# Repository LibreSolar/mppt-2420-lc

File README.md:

# MPPT Charger 20A

 Outdated design, development of new revision ongoing.

**Important:** As we are currently developing a new revision of this charge controller with several improvements, it is not recommended to rebuild this device anymore. Please see [this forum thread](https://talk.libre.solar/t/community-development-of-new-20a-mppt/121) and feel free to contribute your ideas.

## Features:
- 20A MPPT charger (buck converter)
- 55V max PV input
- 12V or 24V battery output
- 32bit ARM MCU (STM32F072)
- CAN communication interface with CANopen standard RJ45 jacks (including 10V power supply)
- Expandable via Olimex Universal Extension Connector (UEXT) featuring I2C, Serial and SPI interface (e.g. used for display, WIFI communication, etc.)
- Compatible to Hammond Mfg 1591XXCFL housing
- 5V switchable signal output
- USB connector for programming etc.
- Can be used as boost converter with software change
- Suitable for Li-Ion batteries with BMS (even recharge after low voltage disconnect possible, as the charge controller increases the voltage automatically when enoug sunlight is available)

## Built-in protection:
- Overvoltage
- Undervoltage
- Overcurrent
- PV short circuit
- PV reverse polarity (for max. module open circuit voltage of around 40V)
- Battery reverse polarity (destructive, fuse is blown)

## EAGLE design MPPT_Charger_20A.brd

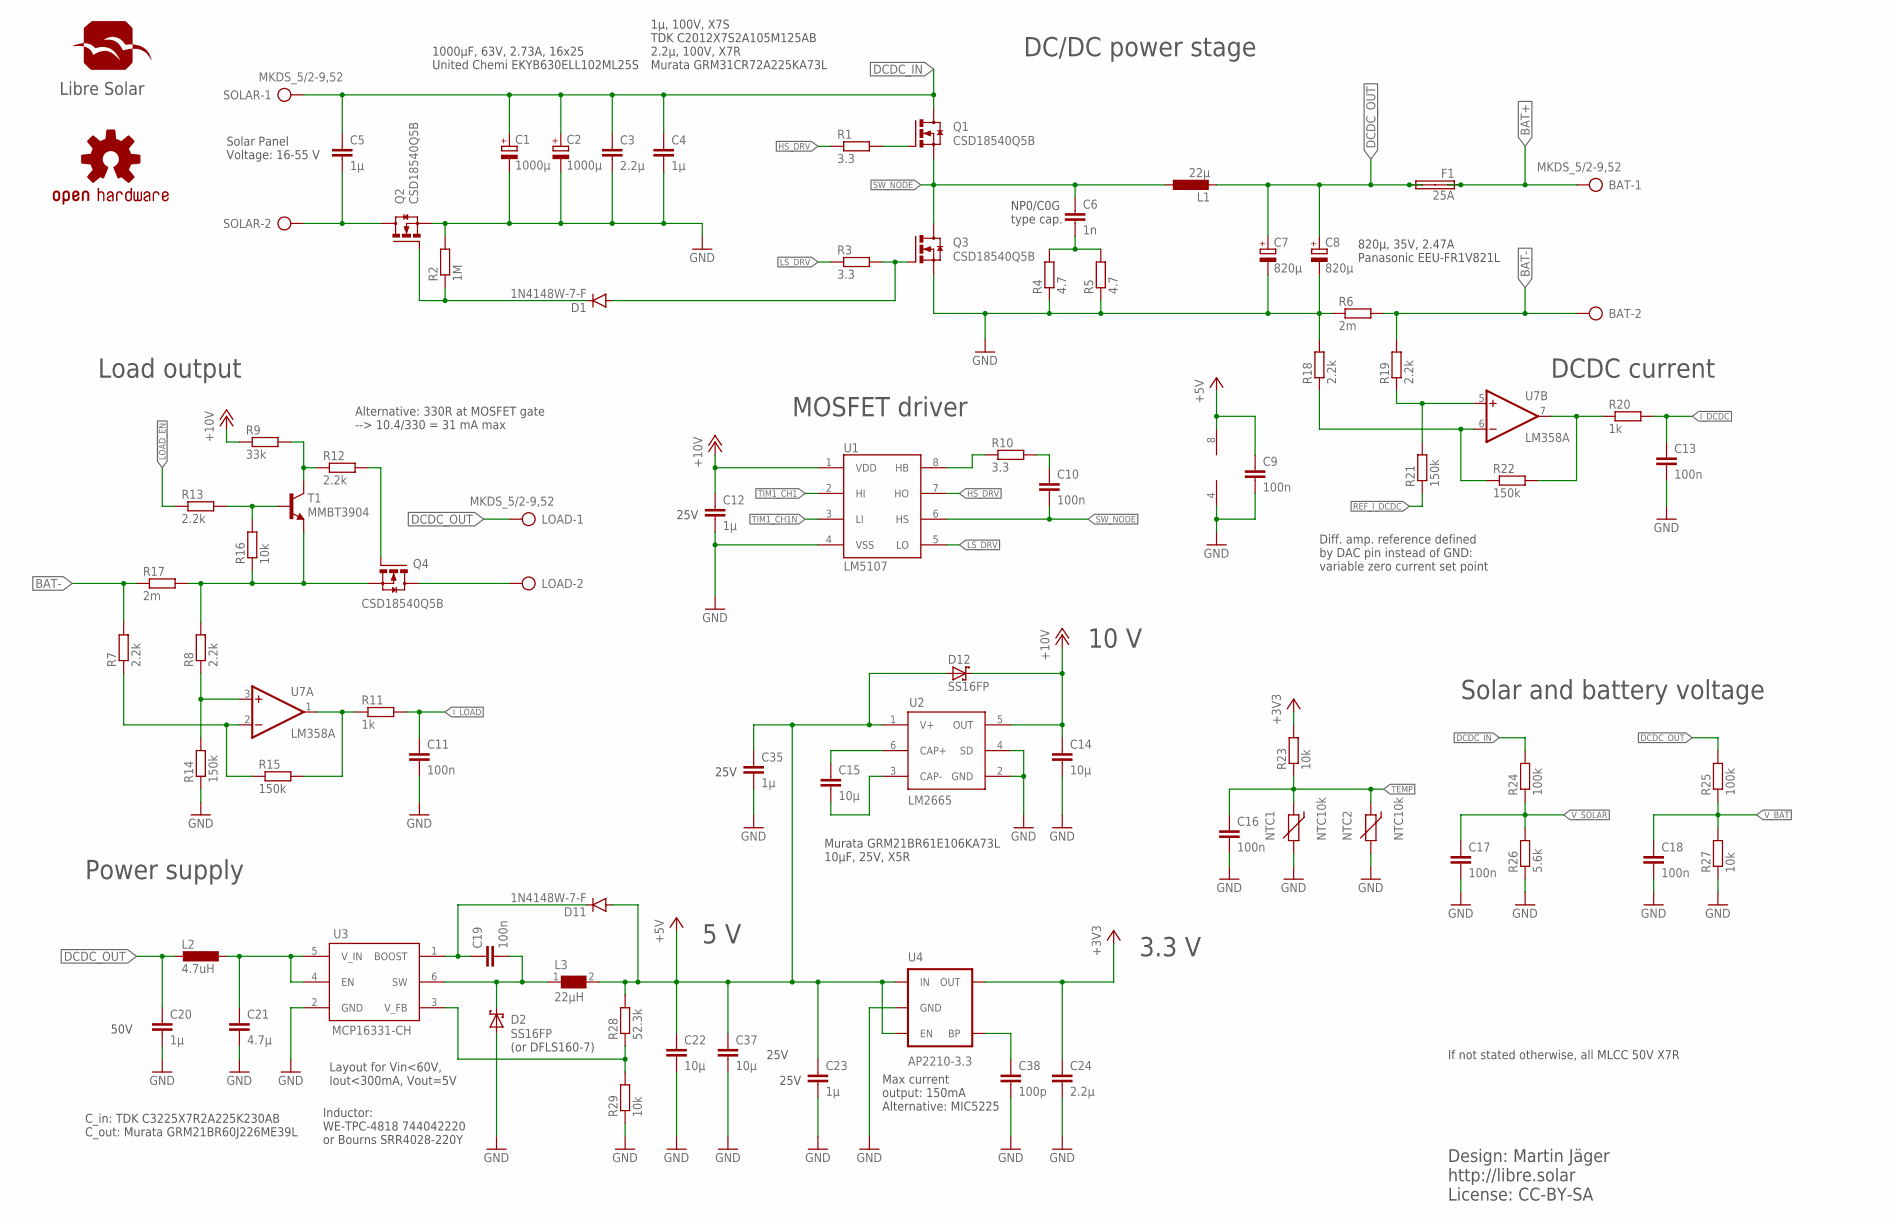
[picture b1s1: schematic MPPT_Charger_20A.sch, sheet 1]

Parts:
BAT: MKDS_5/2-9,52; MKDS_5/2-952; MPN_ALT 691250910002
C1, C2: 1000µ; E7,5-16; MPN EKYB630ELL102ML25S
C3: 2.2µ; C1210
C4, C5, C20: 1µ; C0805
C6: 1n; C0805
C7, C8: 820µ; E5-10,5
C9, C10, C11, C13, C16, C17, C18, C19: 100n; C0603
C12, C23, C35: 1µ; C0603
C14, C15, C22, C37: 10µ; C0805; MPN GRM21BR61E106KA73L
C21: 4.7µ; C1210; MPN GRM31CR71H475KA12L
C24: 2.2µ; C0603; MPN 0805YC475KAT2A
C38: 100p; C0603
D1, D11: 1N4148W-7-F; SOD-123; MPN 1N4148W
D2, D12: SS16FP; POWERDI123; MPN DFLS1100-7
F1: 25A; KEYSTONE-FUSE-3557-2; MPN 3557-2
L1: 22µ; L-FERYSTER-DTMSS-27/0,033/20
L2: 4.7uH; L2012C; MPN 74476404
L3: 22µH; WE-TPC_4818/4828; MPN 744043470
LOAD: MKDS_5/2-9,52; MKDS_5/2-952
N1: OSHW-LOGOM; OSHW-LOGO-M
NTC1, NTC2: NTC10k; R0603@1; MPN NTCG163JF103FT1S
Q1, Q2, Q3, Q4: CSD18540Q5B; 5X6_MOSFET; MPN CSD18540Q5BT
R1, R3, R10: 3.3; R0805; MPN CR0805-FX-1001ELF
R2: 1M; R0603
R4, R5: 4.7; R1206
R6, R17: 2m; R2512; MPN CRE2512-FZ-R002E-3
R7, R8, R12, R13, R18, R19: 2.2k; R0603
R9: 33k; R0603
R11, R20: 1k; R0603
R14, R15, R21, R22: 150k; R0603
R16, R23, R27, R29: 10k; R0603
R24, R25: 100k; R0603
R26: 5.6k; R0603
R28: 52.3k; R0603; MPN CR0805-FX-1001ELF
SOLAR: MKDS_5/2-9,52; MKDS_5/2-952; MPN_ALT 691250910002
T1: MMBT3904; SOT23-BEC; MPN MMBT3904-7-F
U1: LM5107; SOIC-8-N
U2: LM2665; SOT23-6
U3: MCP16331-CH; SOT23-6; MPN MCP16331T-E/CH
U4: AP2210-3.3; SOT23-5; MPN MIC5225-3.3YM5-TR
U7: LM358A; SOIC-8-N
U$1: LIBRESOLAR_LOGO

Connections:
!LOAD_EN!: R13.1; also elsewhere on the board
+3V3: C24.1, R23.2, U4.5 (OUT); also elsewhere on the board
+5V: C9.1, C22.1, C23.1, C35.1, C37.1, D11.A, D12.A, L3.2, R28.2, U2.1 (V+), U4.1 (IN), U4.3 (EN), U7.8 (V+); also elsewhere on the board
+10V: C12.1, C14.1, D12.C, R9.1, U1.1 (VDD), U2.5 (OUT)
BAT+: BAT.1, F1.P$1 (1A), F1.P$2 (1B)
BAT-: BAT.2, R6.2, R7.2, R17.1, R19.2
BAT-1: Q4.S1 (S), Q4.S2 (S), Q4.S3 (S), R8.2, R16.1, R17.2, T1.E
DCDC_IN: C1.+, C2.+, C3.1, C4.1, C5.1, Q1.D, R24.2, SOLAR.1
DCDC_OUT: C7.+, C8.+, C20.1, F1.P$3 (2A), F1.P$4 (2B), L1.P$2 (2), L2.2, LOAD.1, R25.2
GND: C1.-, C2.-, C3.2, C4.2, C7.-, C8.-, C9.2, C11.2, C12.2, C13.2, C14.2, C16.2, C17.2, C18.2, C20.2, C21.2, C22.2, C23.2, C24.2, C35.2, C37.2, C38.2, D2.A, NTC1.2, NTC2.2, Q2.S1 (S), Q2.S2 (S), Q2.S3 (S), Q3.S1 (S), Q3.S2 (S), Q3.S3 (S), R2.2, R4.1, R5.1, R6.1, R14.1, R18.2, R26.1, R27.1, R29.1, U1.4 (VSS), U2.2 (GND), U2.4 (SD), U3.2 (GND), U4.2 (GND), U7.4 (V-); also elsewhere on the board
HB: R10.1, U1.8 (HB)
HS_DRV: R1.1, U1.7 (HO)
I_DCDC: C13.1, R20.2; also elsewhere on the board
I_LOAD: C11.1, R11.2; also elsewhere on the board
LOAD-: LOAD.2, Q4.D
LOAD_G: Q4.G, R12.2
LS_DRV: R3.1, U1.5 (LO)
unnamed: C10.1, R10.2
unnamed: D1.C, Q2.G, R2.1
unnamed: R20.1, R22.2, U7.7 (OUT)
unnamed: D1.A, Q3.G, R3.2
unnamed: R9.2, R12.1, T1.C
unnamed: C6.2, R4.2, R5.2
unnamed: C15.1, U2.6 (CAP+)
unnamed: C15.2, U2.3 (CAP-)
unnamed: R28.1, R29.2, U3.3 (V_FB)
unnamed: R19.1, R21.2, U7.5 (+IN)
unnamed: R8.1, R14.2, U7.3 (+IN)
unnamed: Q1.G, R1.2
unnamed: C19.1, D11.C, U3.1 (BOOST)
unnamed: R18.1, R22.1, U7.6 (-IN)
unnamed: R13.2, R16.2, T1.B
unnamed: C19.2, D2.C, L3.1, U3.6 (SW)
unnamed: C21.1, L2.1, U3.4 (EN), U3.5 (V_IN)
unnamed: C38.1, U4.4 (BP)
unnamed: R11.1, R15.2, U7.1 (OUT)
unnamed: R7.1, R15.1, U7.2 (-IN)
REF_I_DCDC: R21.1; also elsewhere on the board
SOLAR-: C5.2, Q2.D, SOLAR.2
SW_NODE: C6.1, C10.2, L1.P$1 (1), Q1.S1 (S), Q1.S2 (S), Q1.S3 (S), Q3.D, U1.6 (HS)
TEMP: C16.1, NTC1.1, NTC2.1, R23.1; also elsewhere on the board
TIM1_CH1: U1.2 (HI); also elsewhere on the board
TIM1_CH1N: U1.3 (LI); also elsewhere on the board
V_BAT: C18.1, R25.1, R27.2; also elsewhere on the board
V_SOLAR: C17.1, R24.1, R26.2; also elsewhere on the board

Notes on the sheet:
1000µF, 63V, 2.73A, 16x25 United Chemi EKYB630ELL102ML25S
820µ, 35V, 2.47A Panasonic EEU-FR1V821L
Solar Panel Voltage: 16-55 V
Design: Martin Jäger http://libre.solar License: CC-BY-SA
DC/DC power stage
1µ, 100V, X7S TDK C2012X7S2A105M125AB 2.2µ, 100V, X7R Murata GRM31CR72A225KA73L
NP0/C0G type cap.
Load output
DCDC current
MOSFET driver
Solar and battery voltage
Alternative: 330R at MOSFET gate --> 10.4/330 = 31 mA max
Diff. amp. reference defined by DAC pin instead of GND: variable zero current set point
50V
Inductor: WE-TPC-4818 744042220 or Bourns SRR4028-220Y
C_in: TDK C3225X7R2A225K230AB C_out: Murata GRM21BR60J226ME39L
Layout for Vin<60V, Iout<300mA, Vout=5V
Power supply
Max current output: 150mA Alternative: MIC5225
3.3 V
5 V
10 V
If not stated otherwise, all MLCC 50V X7R
(or DFLS160-7)
Murata GRM21BR61E106KA73L 10µF, 25V, X5R
25V

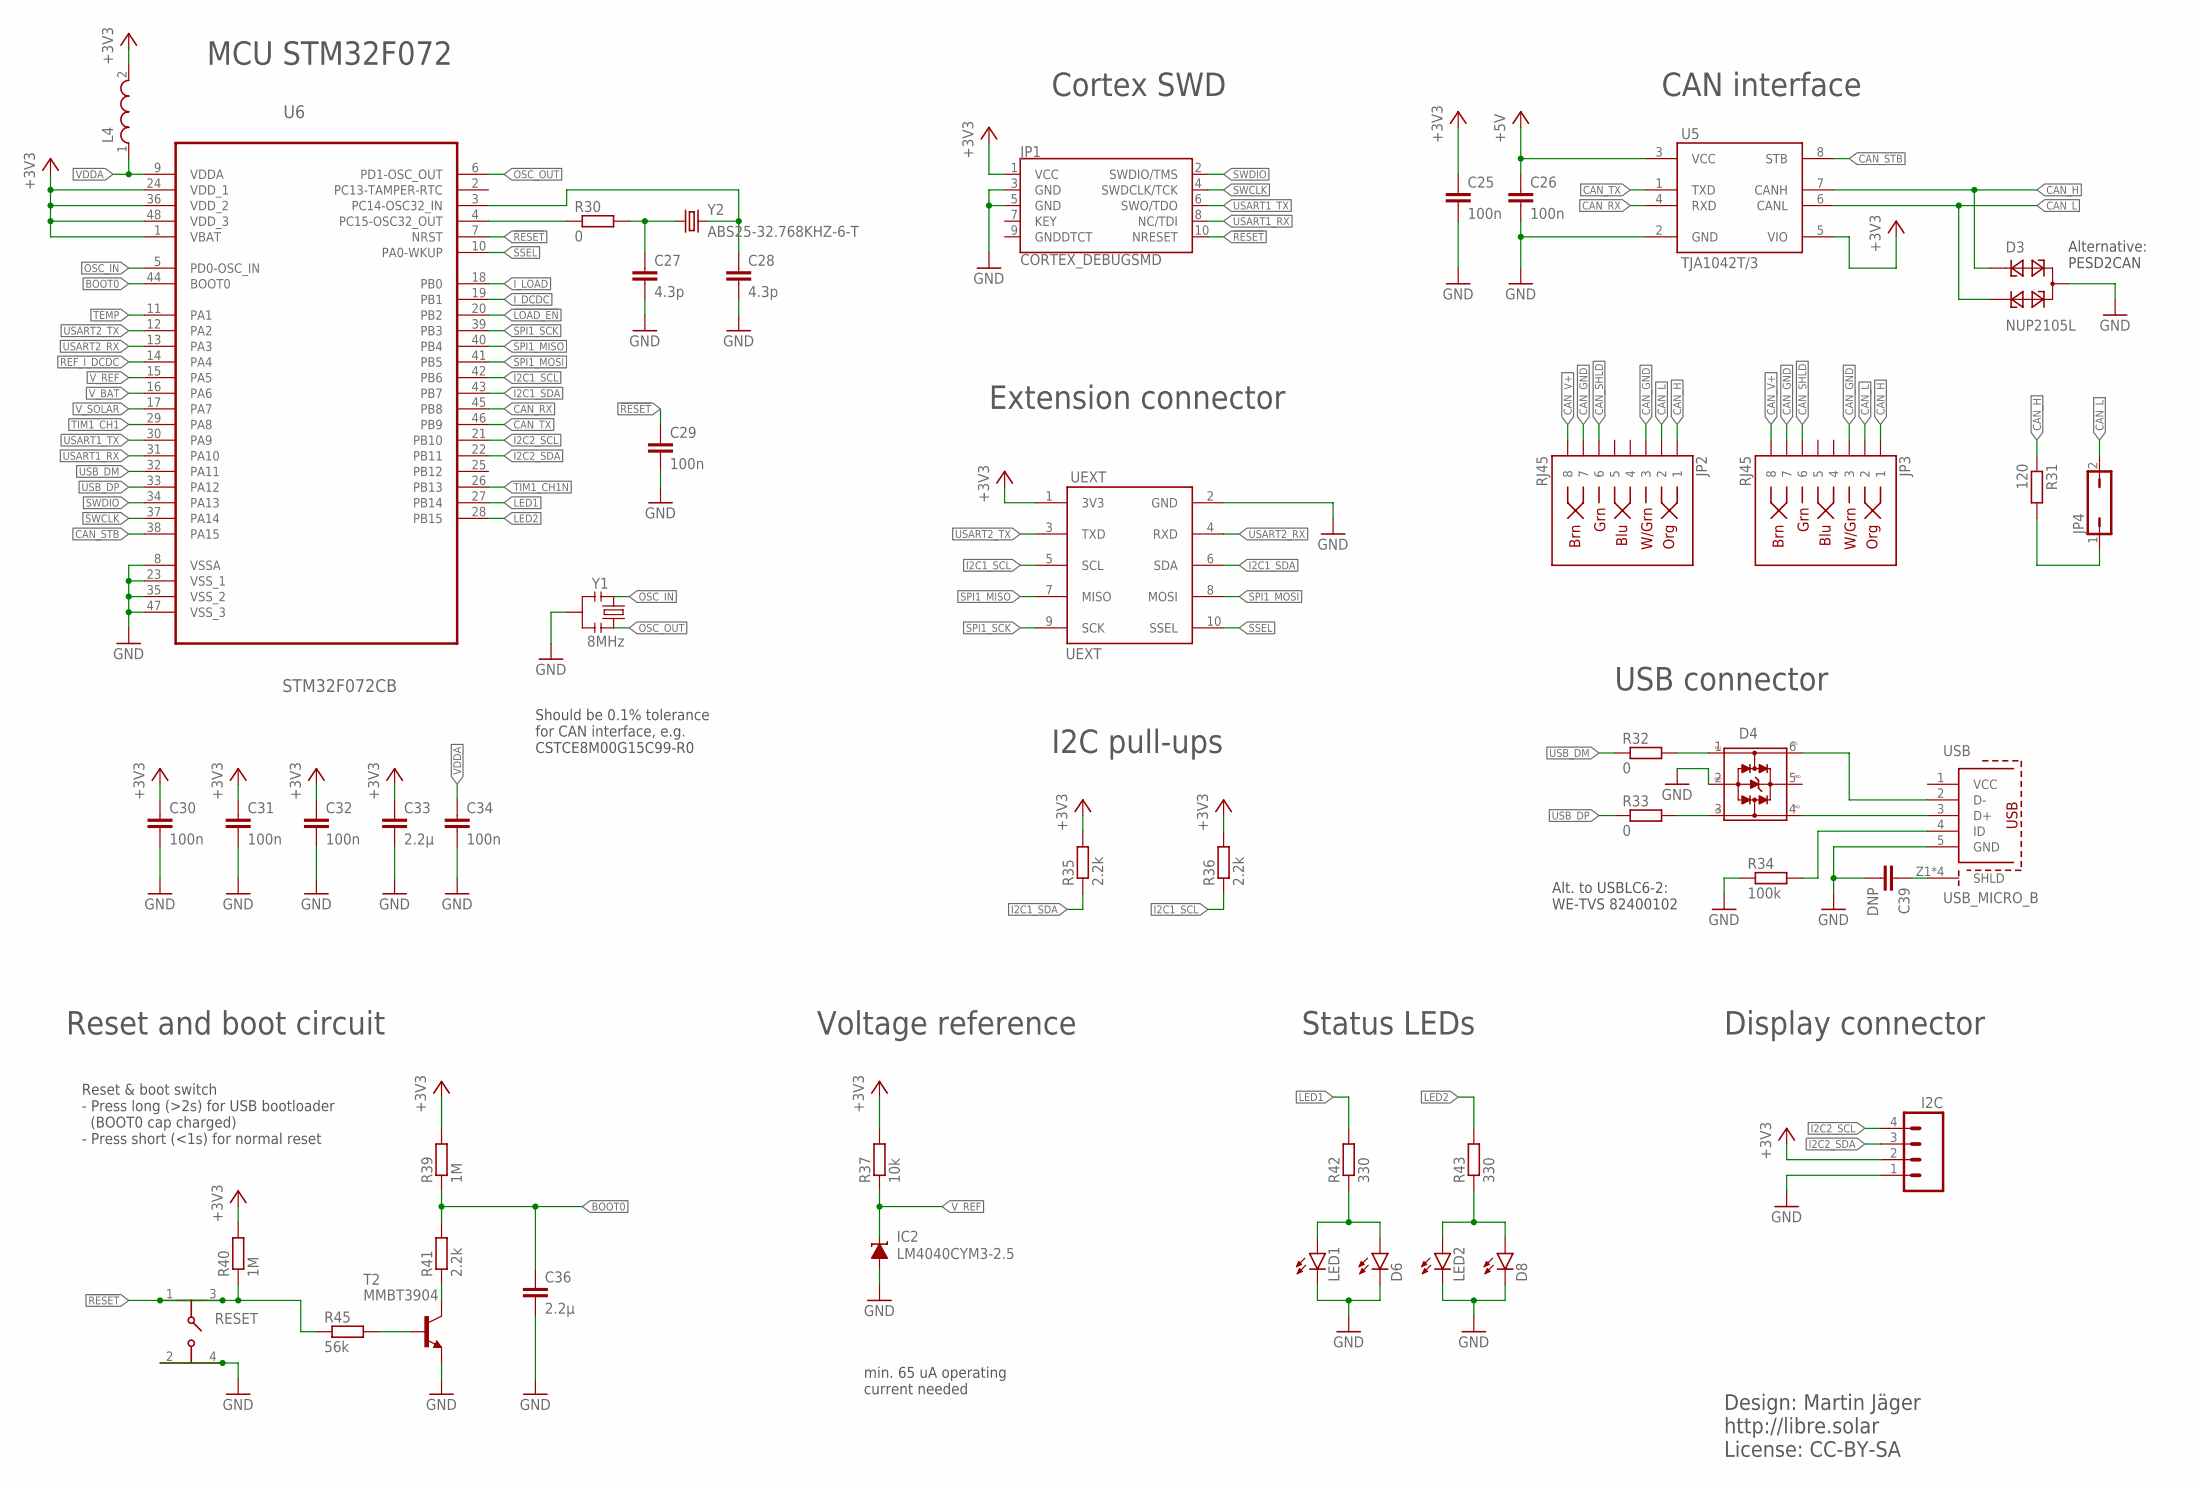
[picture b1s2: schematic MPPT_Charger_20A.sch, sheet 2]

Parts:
C25, C26, C29, C30, C31, C32, C34: 100n; C0603
C27, C28: 4.3p; C0603
C33, C36: 2.2µ; C0603; MPN 0805YC475KAT2A
C39: DNP; C0603
D3: NUP2105L; SOT23; MPN NUP2105LT1G
D4: USBLC6-2; SOT23-6; MPN 82400102
D6, D8: LED0603; LED-0603
I2C: M04PTH; 1X04
IC2: LM4040CYM3-2.5; DBZ_R-PDSO-G3; MPN LM4040DYM3-2.5-TR
JP1: CORTEX_DEBUGSMD; SAMTECH_FTSH-105-01
JP2, JP3: RJ45; RJ45-8; MPN RJHSE-5080
JP4: JP1Q; JP1
L4: WE-CBA_0603(WB/HS); WE-CBA_0603(W=2.2)
LED1, LED2: LED3MM
R30, R32, R33: 0; R0603
R31: 120; R1206
R34: 100k; R0603
R35, R36, R41: 2.2k; R0603
R37: 10k; R0603
R39, R40: 1M; R0603
R42, R43: 330; R0603
R45: 56k; R0603; MPN CR0805-FX-1001ELF
RESET: 430182050816; MPN 430182050816
T2: MMBT3904; SOT23-BEC; MPN MMBT3904-7-F
U5: TJA1042T/3; SOIC-8-N
U6: STM32F072CB; LQFP48
UEXT: UEXT
USB: USB_MICRO_B; USB_MICRO_B_5; MPN 10118192-0001LF
Y1: 8MHz; RESONATOR-SMD-1:1; MPN CSTCE8M00G55-R0
Y2: ABS25-32.768KHZ-6-T; MM20SS; MPN ABS25-32.768KHZ-T

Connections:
!LOAD_EN!: U6.20 (PB2); also elsewhere on the board
!RESET: C29.1, JP1.10 (NRESET), R40.1, R45.1, RESET.1, RESET.3, U6.7 (NRST)
+3V3: C25.1, C30.1, C31.1, C32.1, C33.1, I2C.2, JP1.1 (VCC), L4.2, R35.2, R36.2, R37.2, R39.2, R40.2, U5.5 (VIO), U6.1 (VBAT), U6.24 (VDD_1), U6.36 (VDD_2), U6.48 (VDD_3), UEXT.1 (3V3); also elsewhere on the board
+5V: C26.1, U5.3 (VCC); also elsewhere on the board
BOOT0: C36.1, R39.1, R41.2, U6.44 (BOOT0)
CAN_GND: JP2.3, JP2.7, JP3.3, JP3.7
CAN_H: D3.1, JP2.1, JP3.1, R31.1, U5.7 (CANH)
CAN_L: D3.2, JP2.2, JP3.2, JP4.2, U5.6 (CANL)
CAN_RX: U5.4 (RXD), U6.45 (PB8)
CAN_SHLD: JP2.6, JP3.6
CAN_STB: U5.8 (STB), U6.38 (PA15)
CAN_TX: U5.1 (TXD), U6.46 (PB9)
CAN_V+: JP2.8, JP3.8
GND: C25.2, C26.2, C27.2, C28.2, C29.2, C30.2, C31.2, C32.2, C33.2, C34.2, C36.2, C39.2, D3.3, D4.2 (GND), D6.C, D8.C, I2C.1, IC2.2 (A), JP1.3 (GND), JP1.5 (GND), LED1.K (C), LED2.K (C), R34.1, RESET.2, RESET.4, T2.E, U5.2 (GND), U6.8 (VSSA), U6.23 (VSS_1), U6.35 (VSS_2), U6.47 (VSS_3), UEXT.2 (GND), USB.5 (GND), Y1.2; also elsewhere on the board
I2C1_SCL: R36.1, U6.42 (PB6), UEXT.5 (SCL)
I2C1_SDA: R35.1, U6.43 (PB7), UEXT.6 (SDA)
I2C2_SCL: I2C.4, U6.21 (PB10)
I2C2_SDA: I2C.3, U6.22 (PB11)
I_DCDC: U6.19 (PB1); also elsewhere on the board
I_LOAD: U6.18 (PB0); also elsewhere on the board
LED1: R42.2, U6.27 (PB14)
LED2: R43.2, U6.28 (PB15)
unnamed: D4.1 (I/O1), R32.2
unnamed: R45.2, T2.B
unnamed: R30.1, U6.4 (PC15-OSC32_OUT)
unnamed: D4.3 (I/O2), R33.2
unnamed: D4.4 (I/O2-1), USB.3 (D+)
unnamed: C27.1, R30.2, Y2.1
unnamed: C28.1, U6.3 (PC14-OSC32_IN), Y2.4 (2)
unnamed: R41.1, T2.C
unnamed: D4.6 (I/O1-1), USB.2 (D-)
unnamed: R34.2, USB.4 (ID)
unnamed: C39.1, USB.Z1 (SHLD), USB.Z2 (SHLD), USB.Z3 (SHLD), USB.Z4 (SHLD)
unnamed: JP4.1, R31.2
unnamed: D6.A, LED1.A, R42.1
unnamed: D8.A, LED2.A, R43.1
OSC_IN: U6.5 (PD0-OSC_IN), Y1.1
OSC_OUT: U6.6 (PD1-OSC_OUT), Y1.3
REF_I_DCDC: U6.14 (PA4); also elsewhere on the board
SPI1_MISO: U6.40 (PB4), UEXT.7 (MISO)
SPI1_MOSI: U6.41 (PB5), UEXT.8 (MOSI)
SPI1_SCK: U6.39 (PB3), UEXT.9 (SCK)
SSEL: U6.10 (PA0-WKUP), UEXT.10 (SSEL)
SWCLK: JP1.4 (SWDCLK/TCK), U6.37 (PA14)
SWDIO: JP1.2 (SWDIO/TMS), U6.34 (PA13)
TEMP: U6.11 (PA1); also elsewhere on the board
TIM1_CH1: U6.29 (PA8); also elsewhere on the board
TIM1_CH1N: U6.26 (PB13); also elsewhere on the board
USART1_RX: JP1.8 (NC/TDI), U6.31 (PA10)
USART1_TX: JP1.6 (SWO/TDO), U6.30 (PA9)
USART2_RX: U6.13 (PA3), UEXT.4 (RXD)
USART2_TX: U6.12 (PA2), UEXT.3 (TXD)
USB_DM: R32.1, U6.32 (PA11)
USB_DP: R33.1, U6.33 (PA12)
VCC: USB.1 (VCC)
VDD: D4.5 (VDD)
VDDA: C34.1, L4.1, U6.9 (VDDA)
V_BAT: U6.16 (PA6); also elsewhere on the board
V_REF: IC2.1 (C), R37.1, U6.15 (PA5)
V_SOLAR: U6.17 (PA7); also elsewhere on the board

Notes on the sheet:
Design: Martin Jäger http://libre.solar License: CC-BY-SA
Status LEDs
MCU STM32F072
Extension connector
I2C pull-ups
Should be 0.1% tolerance for CAN interface, e.g. CSTCE8M00G15C99-R0
USB connector
Cortex SWD
Alt. to USBLC6-2: WE-TVS 82400102
CAN interface
Alternative: PESD2CAN
Reset & boot switch - Press long (>2s) for USB bootloader (BOOT0 cap charged) - Press short (<1s) for normal reset
min. 65 uA operating current needed
Voltage reference
Display connector
Reset and boot circuit

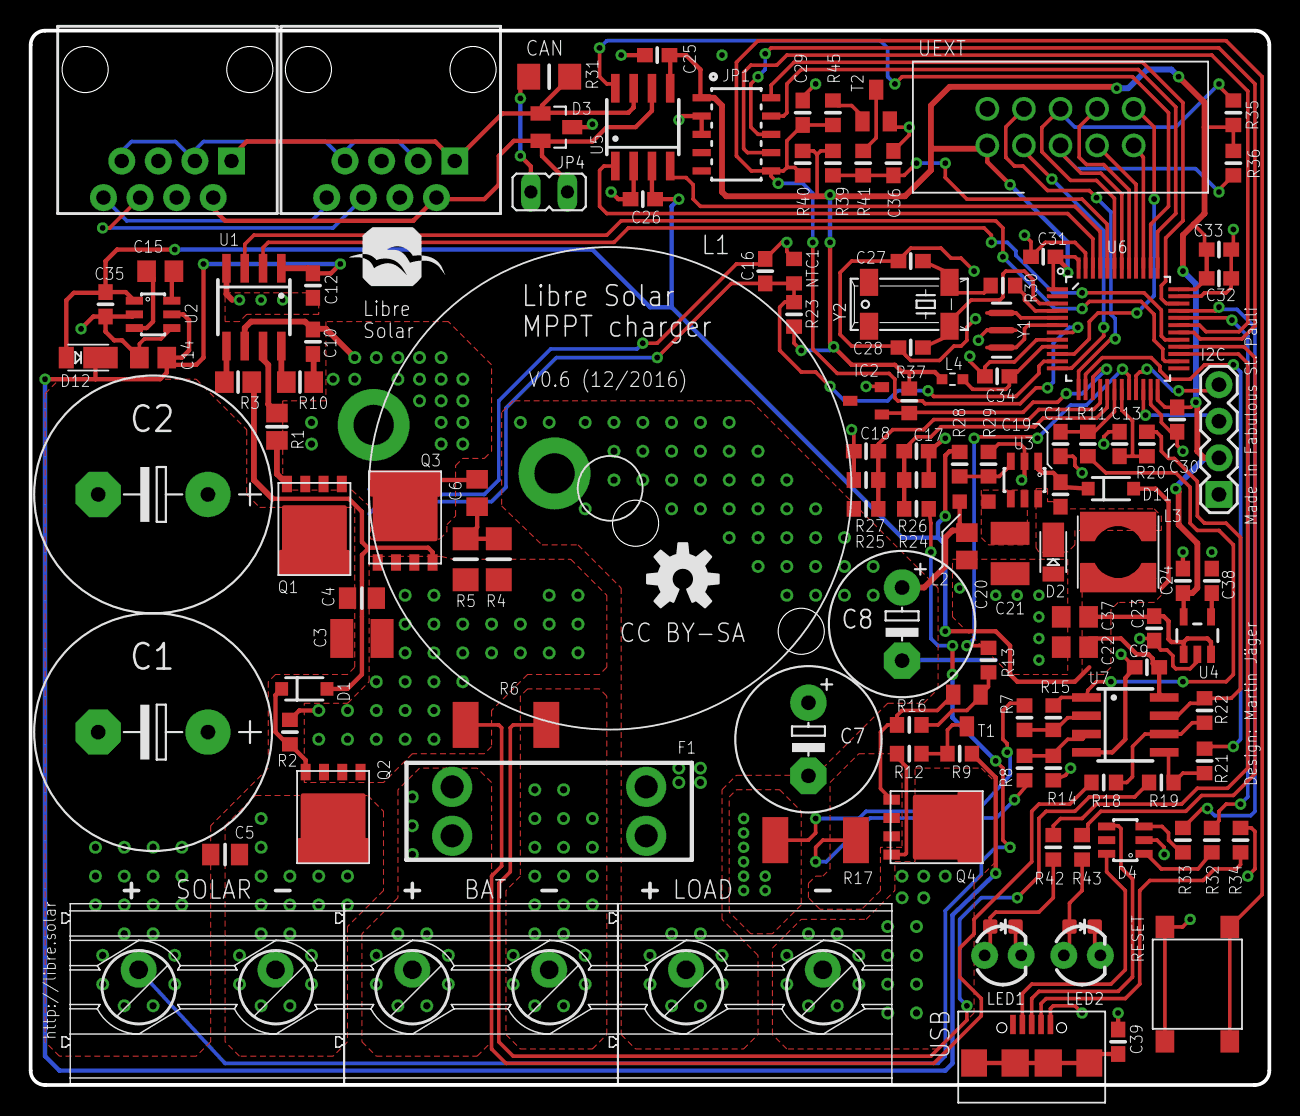
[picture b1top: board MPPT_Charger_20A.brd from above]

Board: 2 copper layers, 86.0 x 73.2 mm, 128 parts (1 on the bottom side), 91 nets.

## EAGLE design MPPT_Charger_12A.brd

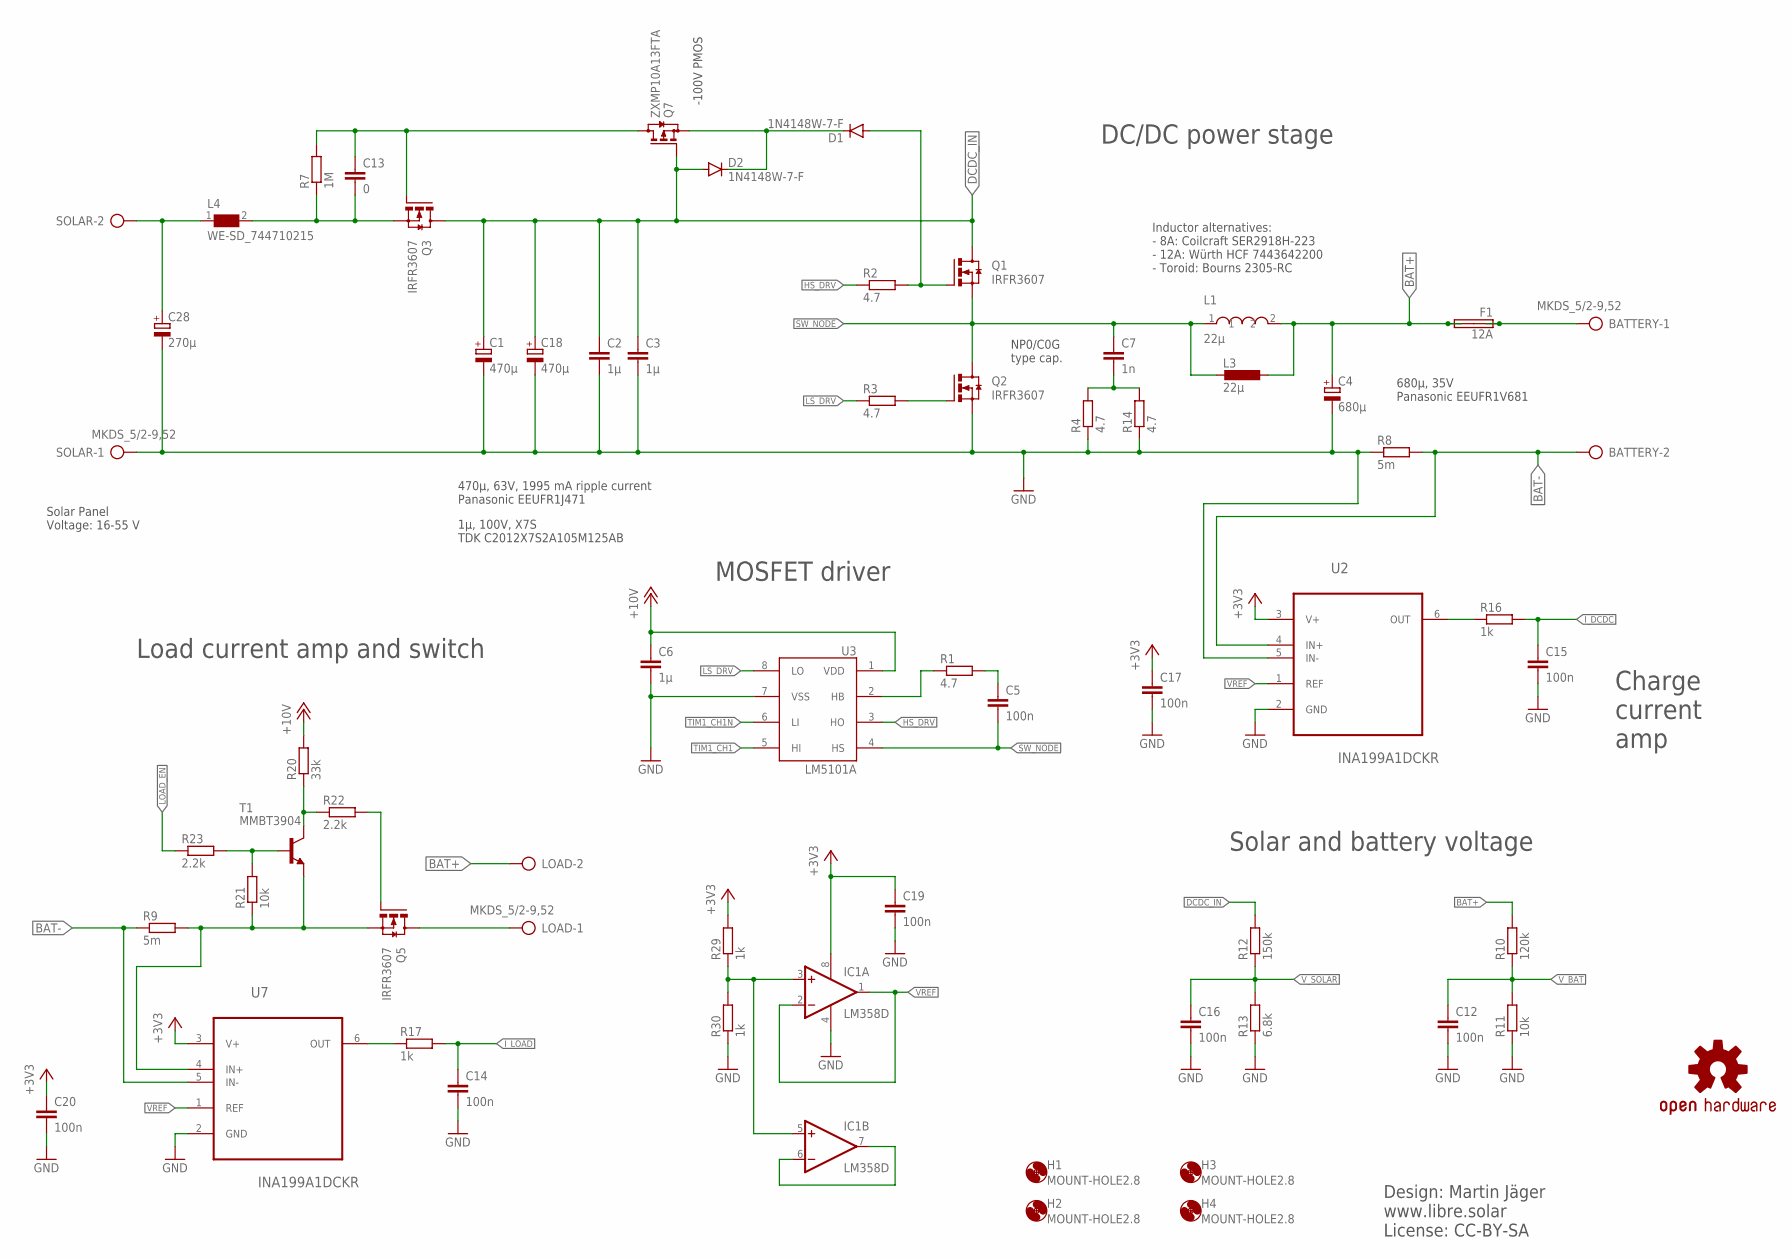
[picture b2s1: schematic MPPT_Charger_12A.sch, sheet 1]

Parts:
BATTERY: MKDS_5/2-9,52; MKDS_5/2-952
C1, C18: 470µ; E5-13; MPN EEUFR1J471B
C2, C3: 1µ; C0805; MPN C2012X7S2A105M125AB
C4: 680µ; E5-10,5; MPN EEUFR1V681LB
C5, C12, C14, C15, C16, C17, C19, C20: 100n; C0603; MPN GRM188R71H104KA93D
C6: 1µ; C0603; MPN 08055C104KAT2A
C7: 1n; C0805; MPN MCU0805C102JCT
C13: 0; C0603; MPN 08055C104KAT2A
C28: 270µ; E5-10,5; MPN EEUFR1J271LB
D1, D2: 1N4148W-7-F; SOD-123; MPN 1N4148W
F1: 12A; BLADE_FUSE_STD; MPN 3522-2
H1, H2, H3, H4: MOUNT-HOLE2.8; 2,8
IC1: LM358D; SO08
L1: 22µ; WE-HCF_2818_7443643300; MPN SER2918H-223KL
L3: 22µ; L-BOURNS-2300-H; MPN 2305-V-RC
L4: WE-SD_744710215; MPN 744710215
LOAD: MKDS_5/2-9,52; MKDS_5/2-952
N1: OSHW-LOGOM; OSHW-LOGO-M
Q1, Q2, Q3, Q5: IRFR3607; DPAK; MPN IRFR3607TRPBF
Q7: ZXMP10A13FTA; SOT23; MPN ZXMP10A13FTA
R1, R2, R3: 4.7; R0805; MPN CR0805-FX-1001ELF
R4, R14: 4.7; R1206; MPN RC1206FR-074R7L
R7: 1M; R0603; MPN RC0603FR-071ML
R8, R9: 5m; R2512; MPN CRF2512-FX-R005ELF
R10: 120k; R0603; MPN RC0603FR-07120KL
R11, R21: 10k; R0603; MPN RC0603FR-0710KL
R12: 150k; R0603; MPN RC0603FR-07150KL
R13: 6.8k; R0603; MPN RC0603FR-076K8L
R16, R17, R29, R30: 1k; R0603; MPN RC0603FR-071KL.
R20: 33k; R0603; MPN RC0603FR-0733KL
R22, R23: 2.2k; R0603; MPN RC0603FR-072K2L.
SOLAR: MKDS_5/2-9,52; MKDS_5/2-952
T1: MMBT3904; SOT23-BEC; MPN MMBT3904-7-F
U2, U7: INA199A1DCKR; SOT65P210X110-6N
U3: LM5101A; SOIC-8-N; MPN LM5101AM/NOPB

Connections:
+3V3: C17.1, C19.1, C20.1, IC1.8 (V+), R29.2, U2.3 (V+), U7.3 (V+); also elsewhere on the board
+10V: C6.1, R20.2, U3.1 (VDD); also elsewhere on the board
BAT+: C4.+, F1.P$3 (2A), F1.P$4 (2B), L1.2, L3.P$1 (1), LOAD.2, R10.2; also elsewhere on the board
BAT-: BATTERY.2, R8.2, R9.1, U2.4 (IN+), U7.5 (IN-)
BAT-1: Q5.3 (S), R9.2, R21.1, T1.E, U7.4 (IN+)
DCDC_IN: C1.+, C2.1, C3.1, C18.+, D2.A, Q1.4 (D), Q3.4 (D), Q7.1 (G), R12.2
FUSE+: BATTERY.1, F1.P$1 (1A), F1.P$2 (1B)
GND: C1.-, C2.2, C3.2, C4.-, C6.2, C12.2, C14.2, C15.2, C16.2, C17.2, C18.-, C19.2, C20.2, C28.-, IC1.4 (V-), Q2.3 (S), R4.1, R8.1, R11.1, R13.1, R14.1, R30.1, SOLAR.1, U2.2 (GND), U2.5 (IN-), U3.7 (VSS), U7.2 (GND); also elsewhere on the board
HS_DRV: R2.1, U3.3 (HO)
I_DCDC: C15.1, R16.2; also elsewhere on the board
I_LOAD: C14.1, R17.2; also elsewhere on the board
LC_OUT: C13.2, L4.2, Q3.3 (S), R7.1
LOAD-: LOAD.1, Q5.4 (D)
LOAD_EN: R23.1; also elsewhere on the board
LOAD_G: Q5.1 (G), R22.2
LS_DRV: R3.1, U3.8 (LO)
unnamed: R1.1, U3.2 (HB)
unnamed: C5.1, R1.2
unnamed: D1.A, Q1.1 (G), R2.2
unnamed: IC1.6 (-IN), IC1.7 (OUT)
unnamed: C13.1, Q3.1 (G), Q7.3 (D), R7.2
unnamed: Q2.1 (G), R3.2
unnamed: D1.C, D2.C, Q7.2 (S)
unnamed: R20.1, R22.1, T1.C
unnamed: C7.2, R4.2, R14.2
unnamed: R16.1, U2.6 (OUT)
unnamed: IC1.3 (+IN), IC1.5 (+IN), R29.1, R30.2
unnamed: R17.1, U7.6 (OUT)
unnamed: R21.2, R23.2, T1.B
SOLAR+: C28.+, L4.1, SOLAR.2
SW_NODE: C5.2, C7.1, L1.1, L3.P$2 (2), Q1.3 (S), Q2.4 (D), U3.4 (HS)
TIM1_CH1: U3.5 (HI); also elsewhere on the board
TIM1_CH1N: U3.6 (LI); also elsewhere on the board
VREF: IC1.1 (OUT), IC1.2 (-IN), U2.1 (REF), U7.1 (REF)
V_BAT: C12.1, R10.1, R11.2; also elsewhere on the board
V_SOLAR: C16.1, R12.1, R13.2; also elsewhere on the board

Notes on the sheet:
470µ, 63V, 1995 mA ripple current Panasonic EEUFR1J471
680µ, 35V Panasonic EEUFR1V681
Solar Panel Voltage: 16-55 V
Design: Martin Jäger www.libre.solar License: CC-BY-SA
DC/DC power stage
1µ, 100V, X7S TDK C2012X7S2A105M125AB
Inductor alternatives: - 8A: Coilcraft SER2918H-223 - 12A: Würth HCF 7443642200 - Toroid: Bourns 2305-RC
-100V PMOS
NP0/C0G type cap.
Load current amp and switch
Charge current amp
MOSFET driver
Solar and battery voltage

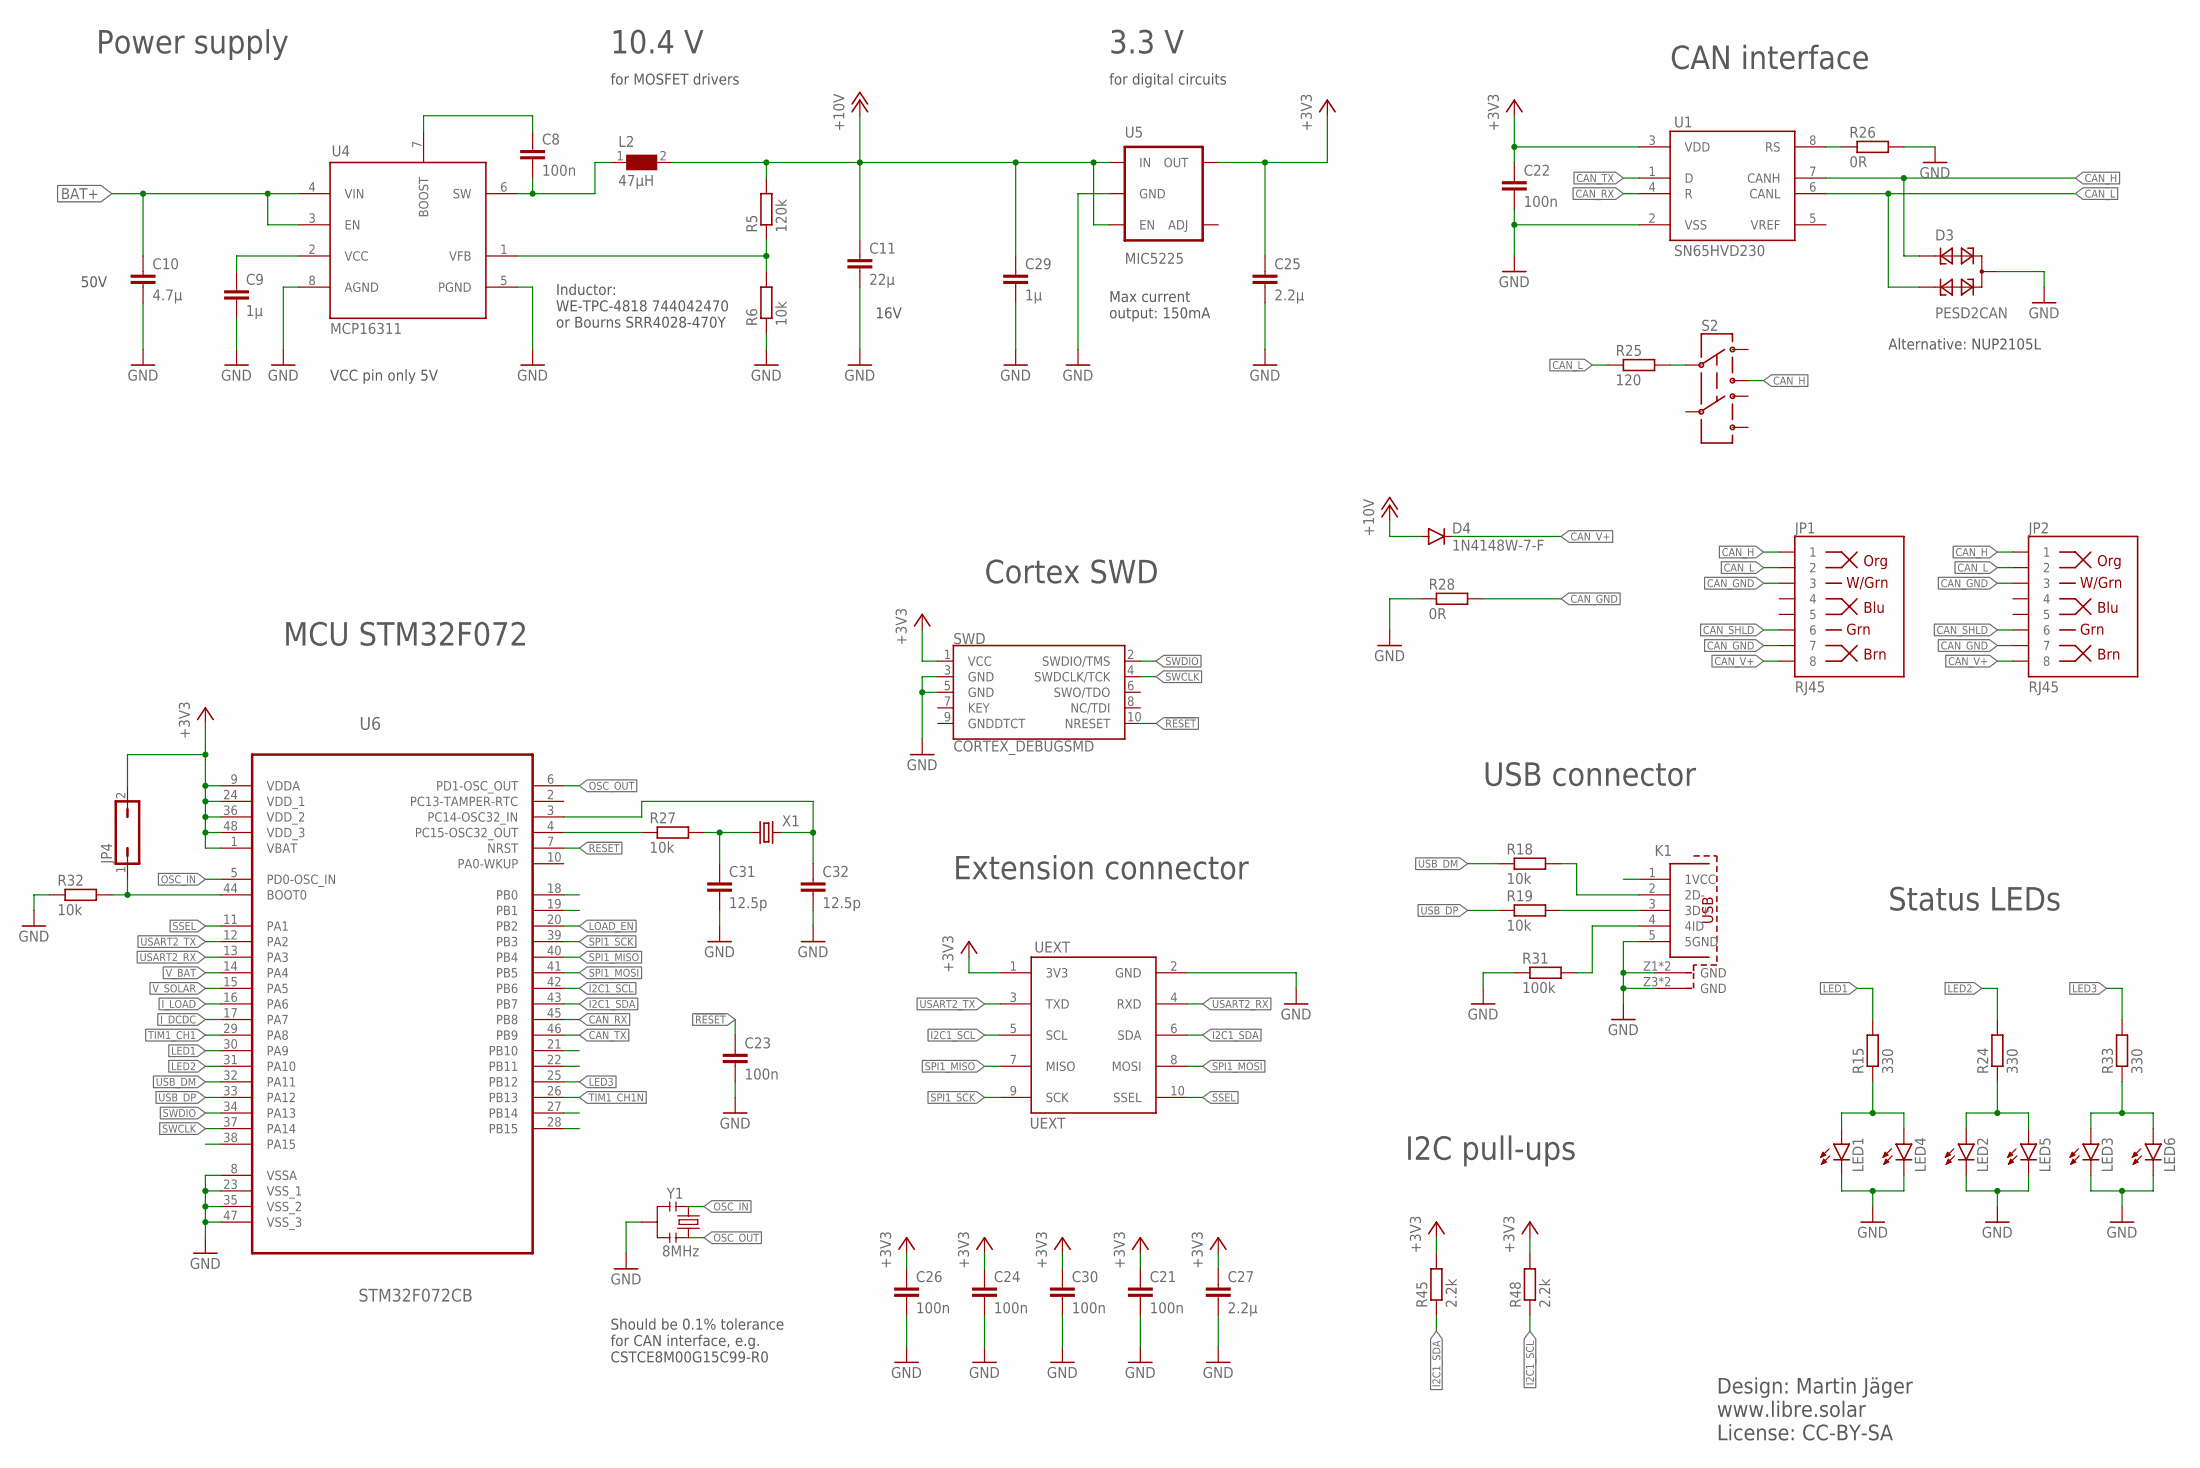
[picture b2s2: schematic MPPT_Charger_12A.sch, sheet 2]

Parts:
C8, C21, C23, C24, C26, C30: 100n; C0603; MPN GRM188R71H104KA93D
C9, C29: 1µ; C0603; MPN 08055C104KAT2A
C10: 4.7µ; C1210; MPN GRM31CR71H475KA12L
C11: 22µ; C1210; MPN MC1210B226M160CT
C22: 100n; C0603; MPN 06035C104KAT2A
C25, C27: 2.2µ; C0603; MPN 0805YC475KAT2A
C31, C32: 12.5p; C0603; MPN GRM188R71H104KA93D
D3: PESD2CAN; SOT23; MPN PESD2CAN
D4: 1N4148W-7-F; SOD-123; MPN 1N4148W
JP1, JP2: RJ45; RJ45-8; MPN RJHSE-5080
JP4: JP1Q; JP1
K1: 629105150521
L2: 47µH; WE-TPC_4818/4828; MPN 744043470
LED1, LED2, LED3: LED3MM
LED4, LED5, LED6: LED0603; LED-0603
R5: 120k; R0603; MPN RC0603FR-07120KL
R6, R18, R19, R27, R32: 10k; R0603; MPN RC0603FR-0710KL
R15, R24, R33: 330; R0603; MPN RC0603FR-07330RL
R25: 120; R1206; MPN WCR0805-120RFI
R26, R28: 0R; R0603; MPN ERJ3GEY0R00V
R31: 100k; R0603; MPN RC0603FR-0710KL
R45, R48: 2.2k; R0603; MPN RC0603FR-072K2L.
S2: SWITCH-DPDT_CK_JS; SWITCH-CK_JS_THT; MPN JS202011CQN
SWD: CORTEX_DEBUGSMD; SAMTECH_FTSH-105-01
U1: SN65HVD230; SOIC-8-N; MPN SN65HVD230DR
U4: MCP16311; MSOP8; MPN MCP16311-E/MS
U5: MIC5225; SOT23-5; MPN MIC5225-3.3YM5-TR
U6: STM32F072CB; QFP50P900X900X160-48N
UEXT: UEXT
X1: CRYSTALMM20SS; MM20SS
Y1: 8MHz; RESONATOR-SMD-1:1; MPN CSTCE8M00G55-R0

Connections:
!RESET: C23.1, SWD.10 (NRESET), U6.7 (NRST)
+3V3: C21.1, C22.1, C24.1, C25.1, C26.1, C27.1, C30.1, JP4.2, R45.2, R48.2, SWD.1 (VCC), U1.3 (VDD), U5.5 (OUT), U6.1 (VBAT), U6.9 (VDDA), U6.24 (VDD_1), U6.36 (VDD_2), U6.48 (VDD_3), UEXT.1 (3V3); also elsewhere on the board
+10V: C11.1, C29.1, D4.A, L2.2, R5.2, U5.1 (IN), U5.3 (EN); also elsewhere on the board
BAT+: C10.1, U4.3 (EN), U4.4 (VIN); also elsewhere on the board
CAN_GND: JP1.3, JP1.7, JP2.3, JP2.7, R28.2
CAN_H: D3.1, JP1.1, JP2.1, S2.P$3 (3), U1.7 (CANH)
CAN_L: D3.2, JP1.2, JP2.2, R25.1, U1.6 (CANL)
CAN_RX: U1.4 (R), U6.45 (PB8)
CAN_SHLD: JP1.6, JP2.6
CAN_TX: U1.1 (D), U6.46 (PB9)
CAN_V+: D4.C, JP1.8, JP2.8
GND: C9.2, C10.2, C11.2, C21.2, C22.2, C23.2, C24.2, C25.2, C26.2, C27.2, C29.2, C30.2, C31.2, C32.2, D3.3, K1.5 (5GND), K1.Z1 (GND), K1.Z2 (GND), K1.Z3 (GND), K1.Z4 (GND), LED1.K (C), LED2.K (C), LED3.K (C), LED4.C, LED5.C, LED6.C, R6.1, R26.2, R28.1, R31.1, R32.1, SWD.3 (GND), SWD.5 (GND), U1.2 (VSS), U4.5 (PGND), U4.8 (AGND), U5.2 (GND), U6.8 (VSSA), U6.23 (VSS_1), U6.35 (VSS_2), U6.47 (VSS_3), UEXT.2 (GND), Y1.2; also elsewhere on the board
I2C1_SCL: R48.1, U6.42 (PB6), UEXT.5 (SCL)
I2C1_SDA: R45.1, U6.43 (PB7), UEXT.6 (SDA)
I_DCDC: U6.17 (PA7); also elsewhere on the board
I_LOAD: U6.16 (PA6); also elsewhere on the board
LED1: R15.2, U6.30 (PA9)
LED2: R24.2, U6.31 (PA10)
LED3: R33.2, U6.25 (PB12)
LOAD_EN: U6.20 (PB2); also elsewhere on the board
unnamed: R26.1, U1.8 (RS)
unnamed: R25.2, S2.P$2 (2)
unnamed: R27.1, U6.4 (PC15-OSC32_OUT)
unnamed: C8.2, L2.1, U4.6 (SW)
unnamed: C8.1, U4.7 (BOOST)
unnamed: C31.1, R27.2, X1.1
unnamed: C9.1, U4.2 (VCC)
unnamed: C32.1, U6.3 (PC14-OSC32_IN), X1.4 (2)
unnamed: R5.1, R6.2, U4.1 (VFB)
unnamed: K1.2 (2D-), R18.2
unnamed: K1.3 (3D+), R19.2
unnamed: K1.4 (4ID), R31.2
unnamed: JP4.1, R32.2, U6.44 (BOOT0)
unnamed: LED3.A, LED6.A, R33.1
unnamed: LED1.A, LED4.A, R15.1
unnamed: LED2.A, LED5.A, R24.1
OSC_IN: U6.5 (PD0-OSC_IN), Y1.1
OSC_OUT: U6.6 (PD1-OSC_OUT), Y1.3
SPI1_MISO: U6.40 (PB4), UEXT.7 (MISO)
SPI1_MOSI: U6.41 (PB5), UEXT.8 (MOSI)
SPI1_SCK: U6.39 (PB3), UEXT.9 (SCK)
SSEL: U6.11 (PA1), UEXT.10 (SSEL)
SWCLK: SWD.4 (SWDCLK/TCK), U6.37 (PA14)
SWDIO: SWD.2 (SWDIO/TMS), U6.34 (PA13)
TIM1_CH1: U6.29 (PA8); also elsewhere on the board
TIM1_CH1N: U6.26 (PB13); also elsewhere on the board
USART2_RX: U6.13 (PA3), UEXT.4 (RXD)
USART2_TX: U6.12 (PA2), UEXT.3 (TXD)
USB_DM: R18.1, U6.32 (PA11)
USB_DP: R19.1, U6.33 (PA12)
V_BAT: U6.14 (PA4); also elsewhere on the board
V_SOLAR: U6.15 (PA5); also elsewhere on the board

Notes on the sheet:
Power supply
Max current output: 150mA
Design: Martin Jäger www.libre.solar License: CC-BY-SA
16V
50V
VCC pin only 5V
Status LEDs
MCU STM32F072
Extension connector
CAN interface
I2C pull-ups
10.4 V
3.3 V
for MOSFET drivers
for digital circuits
Inductor: WE-TPC-4818 744042470 or Bourns SRR4028-470Y
Alternative: NUP2105L
Should be 0.1% tolerance for CAN interface, e.g. CSTCE8M00G15C99-R0
USB connector
Cortex SWD

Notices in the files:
parts and their libraries:
SparkFun-DiscreteSemi: Licensing: Creative Commons ShareAlike 4.0 International - https://creativecommons.org/licenses/by-sa/4.0
PowerMagnetics: Copyright: Würth Elektronik
